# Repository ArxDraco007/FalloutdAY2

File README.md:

# SoupPCB 

## What is this?

This is Soup, a memorable character from Shenzhen China. I made a PCB design of Soup, that can communicate using morse code.

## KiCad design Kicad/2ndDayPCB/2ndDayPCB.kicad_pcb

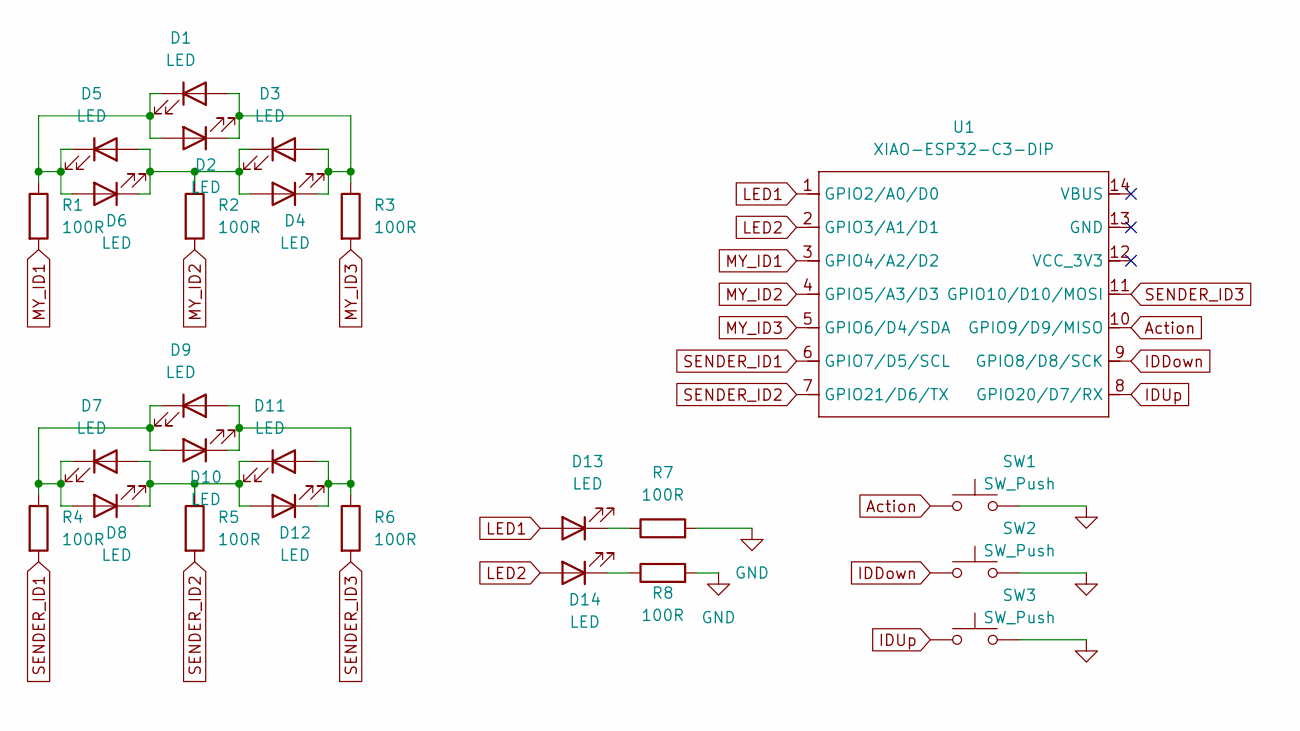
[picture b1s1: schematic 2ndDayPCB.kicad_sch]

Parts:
D1, D2, D3, D4, D5, D6, D7, D8, D9, D10, D11, D12, D13, D14: LED; LED_0805_2012Metric
R1, R2, R3, R4, R5, R6, R7, R8: 100R; R_0805_2012Metric
SW1, SW2, SW3: SW_Push; SW_SPST_TL3342
U1: XIAO-ESP32-C3-DIP

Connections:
Action: SW1.1, U1.10 (GPIO9/D9/MISO)
GND: R7.2, R8.2, SW1.2, SW2.2, SW3.2
IDDown: SW2.1, U1.9 (GPIO8/D8/SCK)
IDUp: SW3.1, U1.8 (GPIO20/D7/RX)
LED1: D13.2 (A), U1.1 (GPIO2/A0/D0)
LED2: D14.2 (A), U1.2 (GPIO3/A1/D1)
MY_ID1: R1.2, U1.3 (GPIO4/A2/D2)
MY_ID2: R2.2, U1.4 (GPIO5/A3/D3)
MY_ID3: R3.2, U1.5 (GPIO6/D4/SDA)
unnamed: D1.2 (A), D2.1 (K), D3.2 (A), D4.1 (K), R3.1
unnamed: D1.1 (K), D2.2 (A), D5.1 (K), D6.2 (A), R1.1
unnamed: D3.1 (K), D4.2 (A), D5.2 (A), D6.1 (K), R2.1
unnamed: D7.1 (K), D8.2 (A), D9.1 (K), D10.2 (A), R4.1
unnamed: D9.2 (A), D10.1 (K), D11.2 (A), D12.1 (K), R6.1
unnamed: D7.2 (A), D8.1 (K), D11.1 (K), D12.2 (A), R5.1
unnamed: D13.1 (K), R7.1
unnamed: D14.1 (K), R8.1
SENDER_ID1: R4.2, U1.6 (GPIO7/D5/SCL)
SENDER_ID2: R5.2, U1.7 (GPIO21/D6/TX)
SENDER_ID3: R6.2, U1.11 (GPIO10/D10/MOSI)

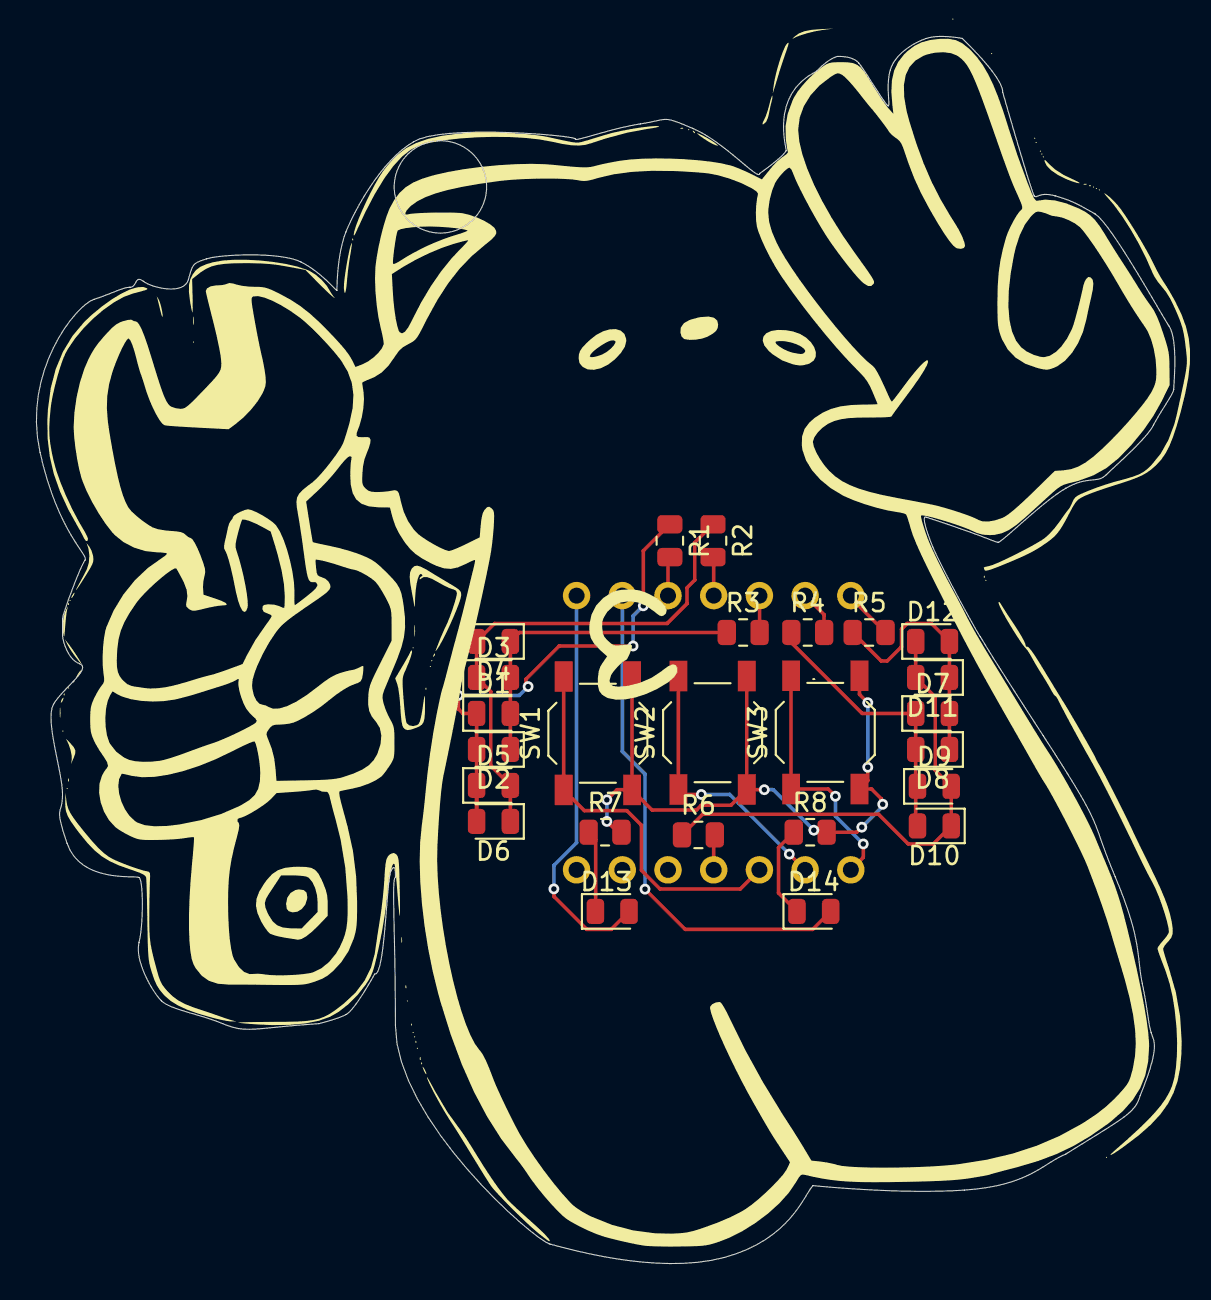
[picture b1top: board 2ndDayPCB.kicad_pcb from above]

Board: 2 copper layers, 63.3 x 68.2 mm, 26 parts (1 on the bottom side), 20 nets.

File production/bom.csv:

Designator,Footprint,Quantity,Value,LCSC Part #
"D1, D10, D11, D12, D13, D14, D2, D3, D4, D5, D6, D7, D8, D9",0805,14,LED,
"R1, R2, R3, R4, R5, R6, R7, R8",0805,8,100R,
"SW1, SW2, SW3",SW_SPST_TL3342,3,SW_Push,
U1,XIAO-ESP32-C3-DIP,1,XIAO-ESP32-C3-DIP,
